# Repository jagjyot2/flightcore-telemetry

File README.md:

# FlightCore — Modular ESP32 Drone Sensor & 433 MHz LoRa Telemetry System

> **STRICT SAFETY CONSTRAINT**: FlightCore is **exclusively a passive sensor acquisition and LoRa telemetry expansion module**. It contains **NO motor/ESC PWM control, NO servo actuation, and NO flight controller stabilization loops**.

---

## System Overview

FlightCore attaches cleanly inline with a `2S–6S` (`7.4 V – 25.2 V`) UAV power bus to acquire inertial attitude, frame vibration, laser altitude, rotor RPM, pack voltage/current/mAh consumption, and thermal probe telemetry, streaming compact **37-byte CRC-16-CCITT binary frames** over **433 MHz LoRa** (`SX1278 Ra-02`) to a companion Python ground station.

```mermaid
flowchart LR
    subgraph Airframe["Airframe Sensors & Power Tap (Strictly Telemetry)"]
        VBAT["2S-6S LiPo -> 1mOhm Shunt + INA180A2 + 100k/10k Div"]
        IMU["MPU6050 IMU (I2C 0x68)"]
        TOF["VL53L0X ToF Laser (I2C 0x29)"]
        HALL["A3144 Hall RPM (ISR GPIO33)"]
        NTC["10k B3950 NTC Probe (GPIO36)"]
    end

    ESP["ESP32 DevKit v1 Firmware (200Hz IMU / 25Hz ToF / 5Hz RF)"]
    LORA["SX1278 433MHz LoRa (VSPI + 50-Ohm SMA)"]
    CAM["ESP32-CAM UART2 Stub (GPIO16/17)"]
    GS["Python Ground Station CLI (CRC-16-CCITT Decoder)"]

    VBAT --> ESP
    IMU --> ESP
    TOF --> ESP
    HALL --> ESP
    NTC --> ESP
    ESP <--> CAM
    ESP --> LORA
    LORA -->|"37B Binary Frame (0xFC 0x01)"| GS
```

---

## Key Engineering Highlights

- **Modular C++17 Firmware (`firmware/`)**:
  - **MPU6050 Driver** ([mpu6050_driver.cpp](firmware/src/mpu6050_driver.cpp)): `400 kHz` I2C, `250`-sample startup bias calibration, complementary roll/pitch filter (`α = 0.98`), and `32`-sample DC-mean-subtracted frame vibration RMS (`mg`).
  - **VL53L0X ToF Driver** ([vl53l0x_driver.cpp](firmware/src/vl53l0x_driver.cpp)): Non-blocking register-level driver with `XSHUT` hardware reset, `5`-tap median + EMA glitch rejection, and timeout diagnostics.
  - **SX1278 433 MHz LoRa Driver & Protocol** ([lora_sx1278.cpp](firmware/src/lora_sx1278.cpp), [telemetry_protocol.cpp](firmware/src/telemetry_protocol.cpp)): `0xFC 0x01` framed 37-byte binary protocol with sequence counter, `CRC-16-CCITT (0x1021/0xFFFF)`, configurable interval (`100–10000 ms`), non-blocking TX retry state machine, and RSSI/SNR link tracking.
  - **Hall-Effect RPM Driver** ([hall_rpm_driver.cpp](firmware/src/hall_rpm_driver.cpp)): `IRAM_ATTR` critical-section ISR on `GPIO33` with `350 µs` glitch debounce, configurable PPR, and timeout zeroing.
  - **Power & Thermal Monitor** ([power_temp_monitor.cpp](firmware/src/power_temp_monitor.cpp)): `16×` oversampled calibrated `ADC1` reads (`VBAT`, `INA180A2` `50 mV/A` current + trapezoidal `mAh` integrator, 3-term Steinhart-Hart NTC temperature).
  - **Diagnostics CLI & ESP32-CAM Bridge** ([main.cpp](firmware/src/main.cpp)): Non-blocking USB Serial CLI (`status`, `json`, `bin`, `hex`, `interval <ms>`, `cal imu`, `reset mah`, `ppr <n>`, `cam ping`) + `UART2` heartbeat bridge stub.
- **Ground Station Decoder (`ground_station/`)**:
  - Byte-exact Python implementation ([protocol.py](ground_station/protocol.py), [receiver_cli.py](ground_station/receiver_cli.py)) supporting live serial (`--serial`), hex dump (`--hex`), binary log playback (`--file`), and synthetic noisy stream simulation (`--simulate --inject-noise`).
- **Manufacturing-Ready KiCad 8 Hardware (`hardware/`)**:
  - Complete schematic, 2-layer `96.0 × 68.0 mm` PCB, netlist, RS-274X Gerbers + Excellon drill (`hardware/gerbers/`), geometric DRC report (`0 errors`), verified BOM ([BOM.csv](hardware/BOM.csv)), [PIN-MAPPING.md](hardware/PIN-MAPPING.md), [POWER-ARCHITECTURE.md](hardware/POWER-ARCHITECTURE.md), and [ASSEMBLY-GUIDE.md](hardware/ASSEMBLY-GUIDE.md).
- **Simulator-Independent Abstraction & Wokwi Simulation (`simulation/`, `wokwi/`)**:
  - Canonical simulator-agnostic sensor/transport interface ([sensor_bus_adapter.h](simulation/adapters/common/sensor_bus_adapter.h), [sensor_bus_adapter.py](simulation/adapters/common/sensor_bus_adapter.py)), deterministic flight/fault scenarios (`simulation/scenarios/`), and explicit [COMPONENT-SUPPORT-MATRIX.md](simulation/documentation/COMPONENT-SUPPORT-MATRIX.md).
  - **Active Wokwi Configuration (`wokwi/`)**: `board-esp32-devkit-c-v4` wired to `wokwi-mpu6050`, `wokwi-ntc-temperature-sensor`, `wokwi-potentiometer` (`VBAT`/`IBAT`), `wokwi-pushbutton` (`HALL_PULSE`/`CAL`), `wokwi-led`, and custom Wokwi chip stubs `chip-vl53l0x` and `chip-sx1278` executing `firmware/.pio/build/esp32dev/firmware.elf`.
- **BenchTwin & 3D CAD Staging (`benchtwin/` — Preserved)**:
  - Structured circuit graph (`flightcore-benchtwin.json`, `flightcore.btw`), vector schematic (`schematic_preview.svg`), simulation notes ([BENCHTWIN-SIMULATION-NOTES.md](benchtwin/BENCHTWIN-SIMULATION-NOTES.md)), and watertight closed-manifold 3D-printable mount (`enclosure_mount.stl`), indexed via [benchtwin_adapter_manifest.json](simulation/adapters/benchtwin/benchtwin_adapter_manifest.json) for future reactivation.

---

## Repository Structure

```
04-FLIGHTCORE/
├── firmware/           # PlatformIO ESP32 C++17 modular drivers, main loop & native C++ tests
├── ground_station/     # Python binary CRC-16-CCITT telemetry decoder & CLI
├── hardware/           # KiCad 8 project, Gerbers, DRC report, BOM & hardware guides
├── simulation/         # Simulator-agnostic adapters (common, wokwi, benchtwin), scenarios & matrix
├── wokwi/              # Active Wokwi diagram.json, wokwi.toml & custom chip stubs (VL53L0X/SX1278)
├── benchtwin/          # Preserved BenchTwin circuit graph/bundle, STL mount & SVG preview
├── tests/              # Automated pytest verification (protocol, math, C++ native, Wokwi, KiCad/STL)
├── docs/               # Detailed system architecture & protocol specs
├── ROADMAP.md          # Engineering phases & passive telemetry roadmap
└── LICENSE             # MIT License
```

---

## Quickstart & Verification

### 1. Build ESP32 Firmware & Static Check (PlatformIO)
```powershell
cd firmware
pio run -e esp32dev
pio check --skip-packages
```

### 2. Run Full Automated Verification Suite (Pytest + Compiled C++17 Native Tests)
```powershell
pytest -v
```
Verifies CRC-16-CCITT, binary encode/decode roundtrips, stream resynchronization, Steinhart-Hart NTC math, complementary filter convergence, vibration RMS, ToF median+EMA glitch rejection, Hall RPM debouncing, strict telemetry-only safety boundary, compiled C++ native tests (`firmware/test/test_flightcore_native.cpp`), KiCad S-expression validity, RS-274X Gerbers, DRC report, BOM/netlist parity, and STL closed-manifold geometry.

### 3. Run Ground Station Decoder CLI Without Hardware
```powershell
python -m ground_station.receiver_cli --simulate --count 6 --inject-noise --format table
```

### 4. Run Active Wokwi Simulation
1. Build firmware (`pio run -e esp32dev` in `firmware/`).
2. Open `wokwi/` in VS Code with the Wokwi extension (or run `wokwi-cli wokwi` with `$env:WOKWI_CLI_TOKEN` set). See [wokwi/README.md](wokwi/README.md) and [simulation/documentation/COMPONENT-SUPPORT-MATRIX.md](simulation/documentation/COMPONENT-SUPPORT-MATRIX.md).

#### Wokwi Component Support Summary
| Component | Wokwi Status | Simulation Representation |
|---|---|---|
| `ESP32 DevKit v1` (`U1`) | Native | `board-esp32-devkit-c-v4` |
| `MPU6050` (`U2`) | Native | `wokwi-mpu6050` (`I2C 0x68`) |
| `10k NTC` (`RT1`) & `SW1` / `D4` | Native | `wokwi-ntc-temperature-sensor`, `wokwi-pushbutton`, `wokwi-led` |
| `VBAT` Divider / `INA180A2` | Analog Stand-In | `wokwi-potentiometer` (`GPIO34` / `GPIO35`) |
| `VL53L0X` (`U3`) & `SX1278` (`U4`) | Unsupported Natively -> Custom Chip Stubs | `wokwi/chips/chip-vl53l0x.*` & `chip-sx1278.*` |
| `A3144` Hall (`U8`) & `ESP32-CAM` (`J6`) | Unsupported Natively -> Pulse/SW Stubs | `wokwi-pushbutton` (`GPIO33`) & UART2 software stub |

#### Future BenchTwin Reactivation
`benchtwin/` is preserved untouched. To reactivate BenchTwin for electrical/3D inspection, open `benchtwin/flightcore.btw` (see [simulation/adapters/benchtwin/README.md](simulation/adapters/benchtwin/README.md)).

---

## Hardware BOM Summary

| Subsystem | Key Part | Interface / Rating | Designator |
|---|---|---|---|
| MCU | DOIT ESP32 DevKit v1 (30-pin) | `3.3 V` IO / `5 V` VIN | `U1` |
| 6-Axis IMU | MPU6050 (GY-521) | `I2C 0x68` @ `400 kHz` | `U2` |
| ToF Ranging | VL53L0X (GY-VL53L0XV2) | `I2C 0x29`, `XSHUT=GPIO26` | `U3` |
| 433 MHz LoRa | AI-Thinker Ra-02 (SX1278) | `VSPI`, `+17 dBm`, Edge SMA `J5` | `U4` |
| Current Sense | `1 mΩ 3W 2512` Shunt + `INA180A2` | `50 mV/A`, `V_CM <= 26 V` | `R11`, `U5` |
| Power Rails | `MP1584 5V/3A Buck` + `AMS1117-3.3` | `2S–6S LiPo` + PTC/Schottky/TVS | `U7`, `U6`, `F1`, `D1`, `D3` |
| RPM & Thermal | `A3144EUA-T` Hall + `10 kΩ B3950 NTC` | `GPIO33` ISR / `GPIO36` ADC1 | `U8`, `RT1` |

See [hardware/BOM.csv](hardware/BOM.csv) and [hardware/ASSEMBLY-GUIDE.md](hardware/ASSEMBLY-GUIDE.md) for complete assembly instructions and the mandatory **`JP1` power jumper rule**.

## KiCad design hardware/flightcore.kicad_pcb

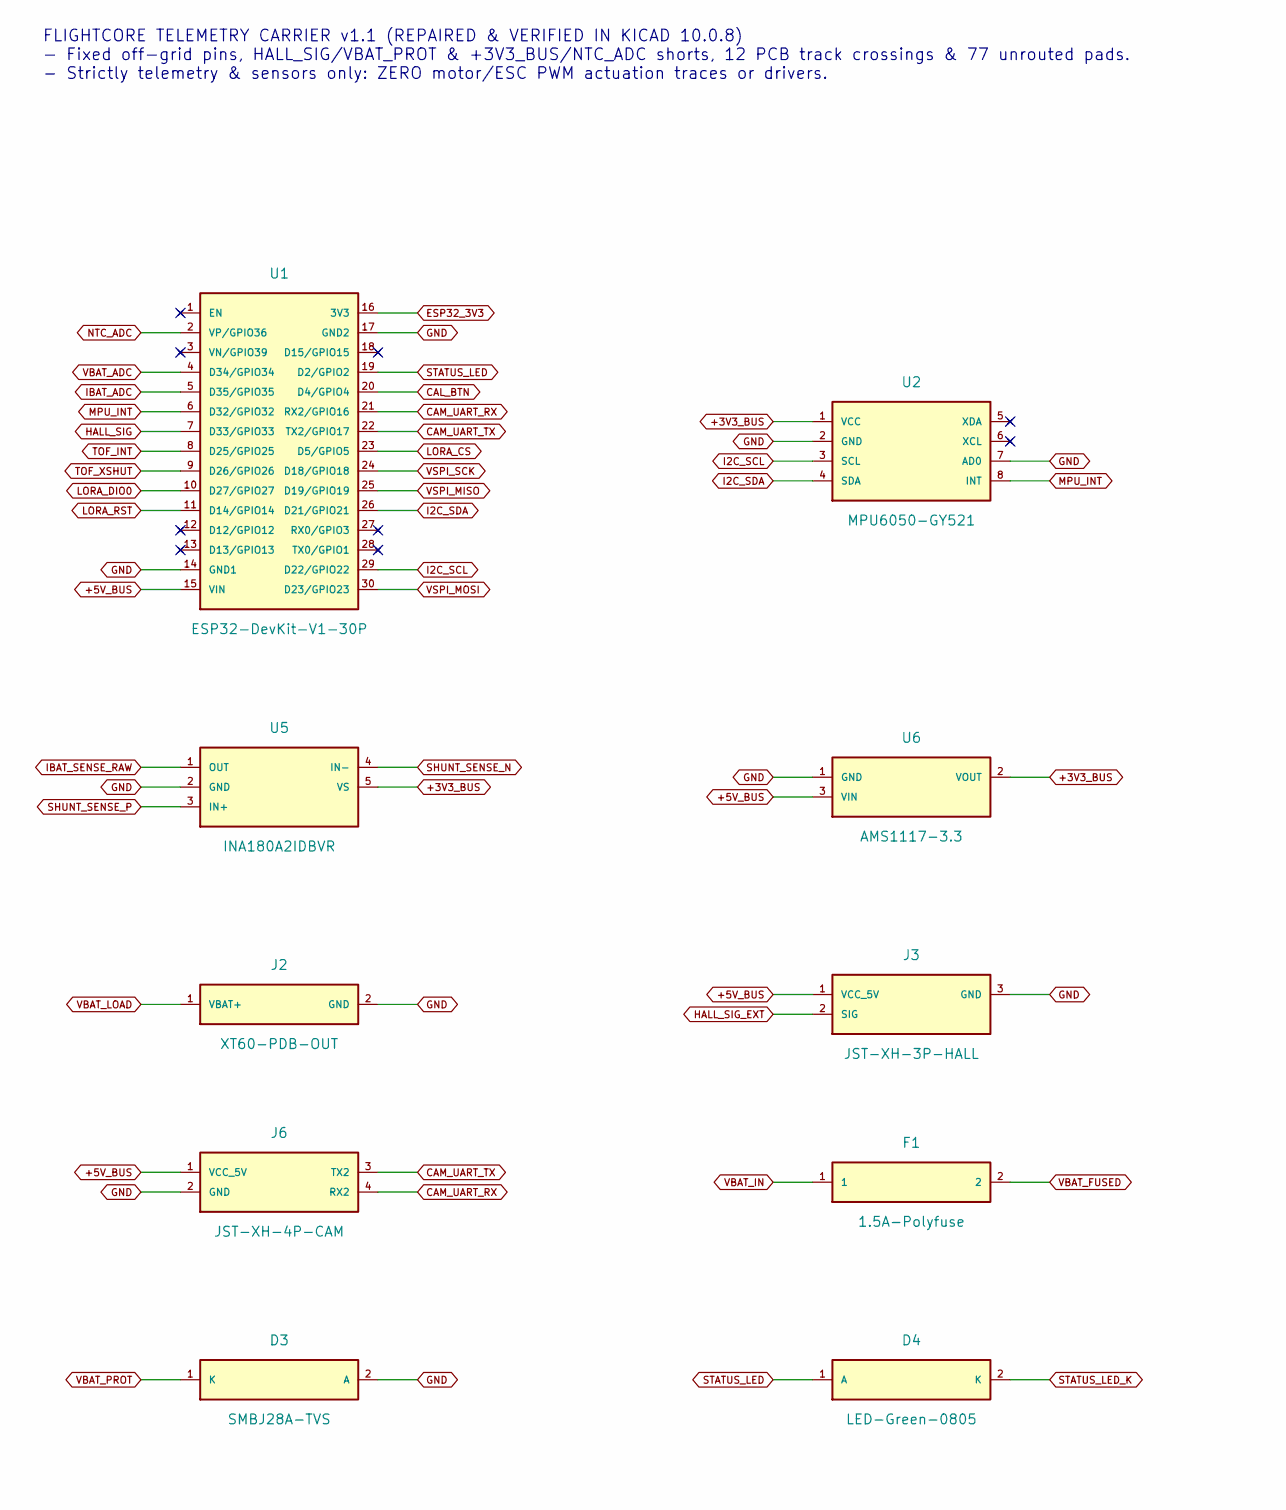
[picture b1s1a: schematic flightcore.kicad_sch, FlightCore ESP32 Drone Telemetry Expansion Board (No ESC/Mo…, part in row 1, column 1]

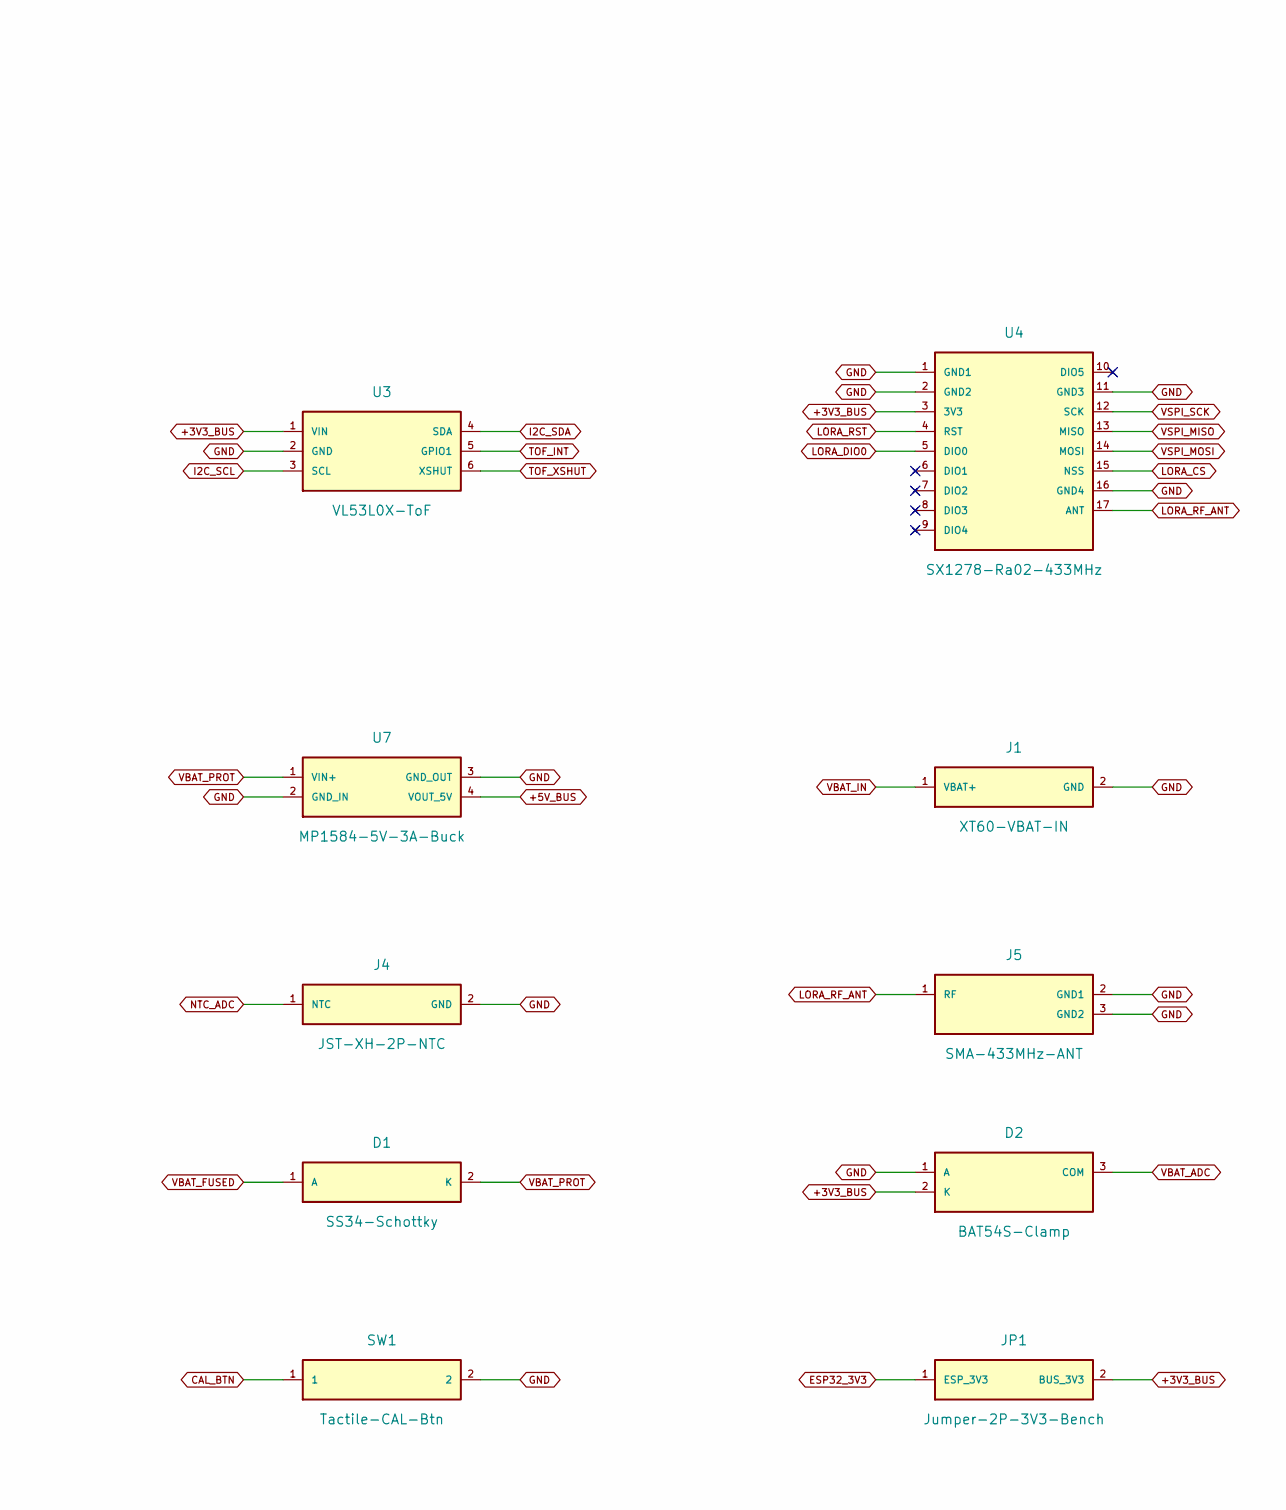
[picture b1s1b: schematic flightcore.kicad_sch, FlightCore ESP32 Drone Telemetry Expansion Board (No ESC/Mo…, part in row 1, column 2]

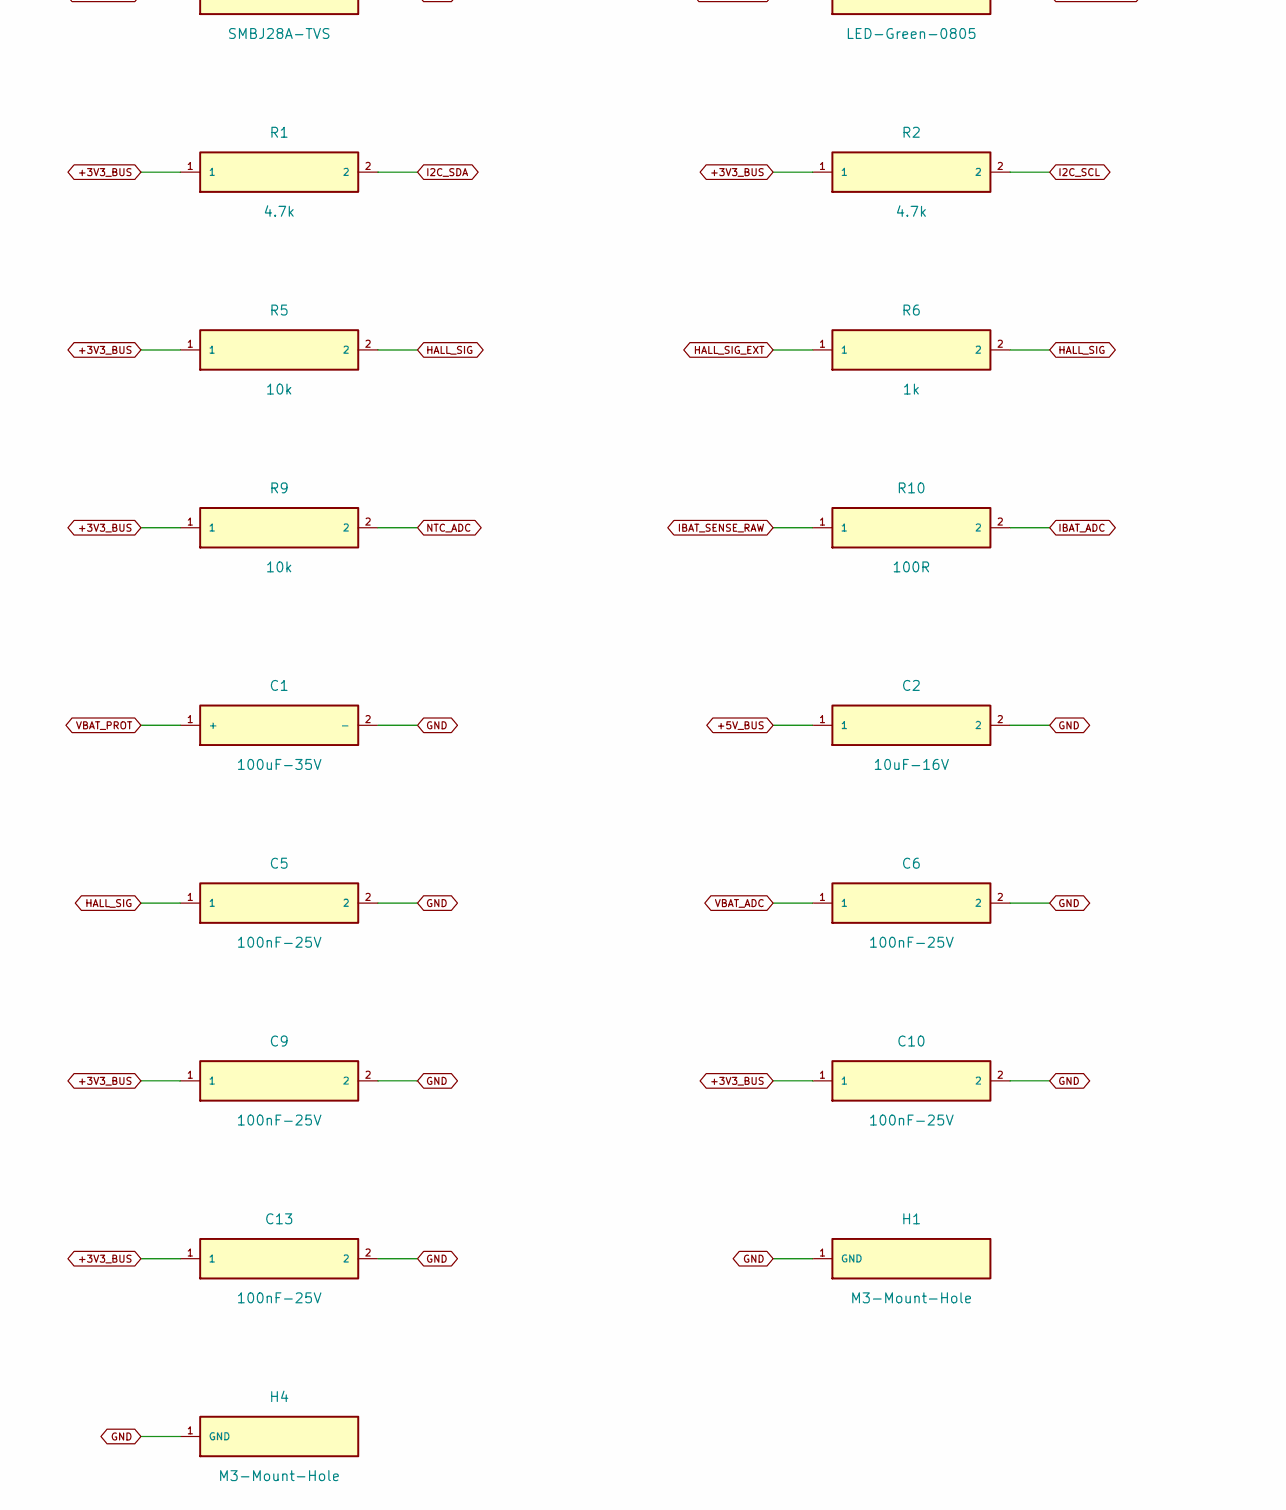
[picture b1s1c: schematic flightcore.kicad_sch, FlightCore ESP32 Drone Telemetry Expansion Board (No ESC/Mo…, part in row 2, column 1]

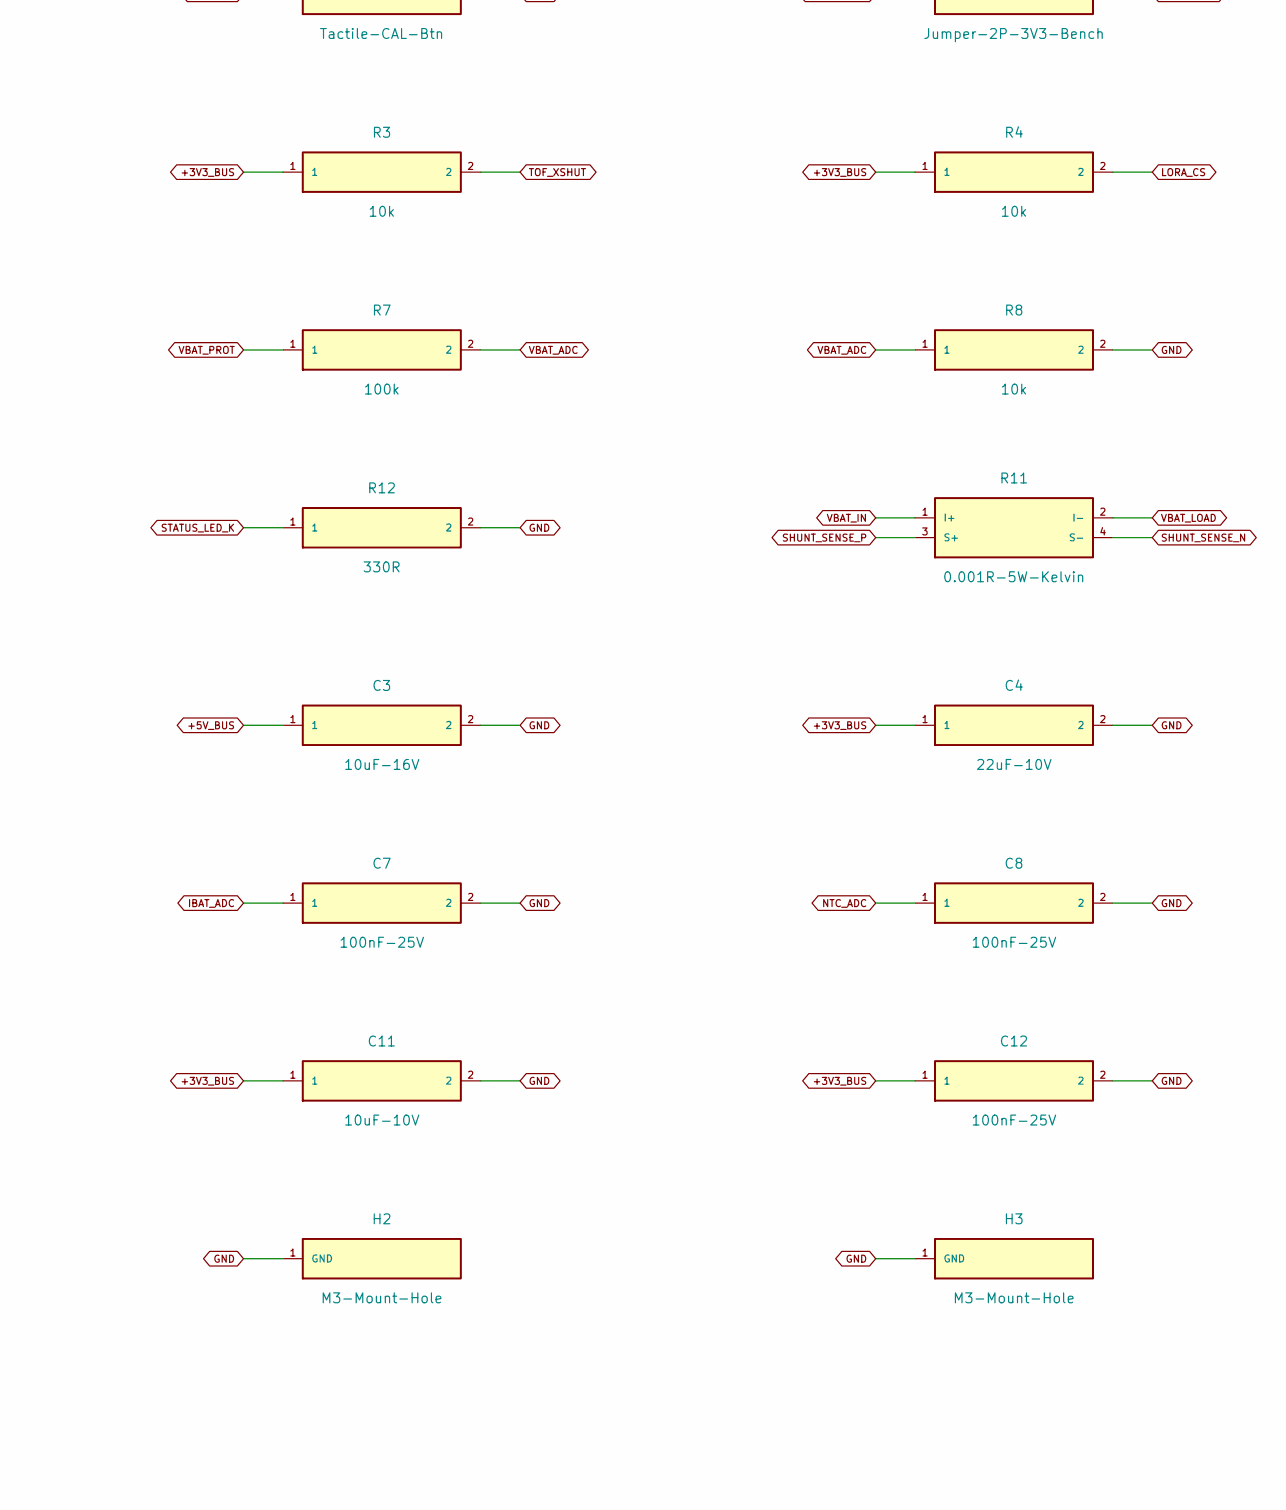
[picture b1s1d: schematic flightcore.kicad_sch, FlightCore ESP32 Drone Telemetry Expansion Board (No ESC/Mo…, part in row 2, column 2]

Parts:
C1: 100uF-35V; CP_Radial_D6.3mm; Rating 35V / 100uF
C2, C3: 10uF-16V; SMD_0805; Rating 16V
C4: 22uF-10V; SMD_0805; Rating 10V
C5, C6, C7, C8, C9, C10, C12, C13: 100nF-25V; SMD_0805; Rating 25V
C11: 10uF-10V; SMD_0805; Rating 10V
D1: SS34-Schottky; D_SMA; Rating 40V / 3A; MPN SS34
D2: BAT54S-Clamp; SOT-23; Rating 30V / 200mA; MPN BAT54S
D3: SMBJ28A-TVS; D_SMB; Rating 28V / 600W; MPN SMBJ28A
D4: LED-Green-0805; SMD_0805; Rating 2.1V / 20mA; MPN APT2012CGCK
F1: 1.5A-Polyfuse; SMD_1206; Rating 30V / 1.5A; MPN 1206L150
H1, H2, H3, H4: M3-Mount-Hole; MountingHole_3.2mm_M3_Pad_Via; Rating M3
J1: XT60-VBAT-IN; AMASS_XT60_Vertical; Rating 60A / 25.2V; MPN XT60-M
J2: XT60-PDB-OUT; AMASS_XT60_Vertical; Rating 60A / 25.2V; MPN XT60-F
J3: JST-XH-3P-HALL; JST_XH_B3B-XH-A_1x03_P2.50mm_Vertical; Rating 5V / 1A; MPN B3B-XH-A
J4: JST-XH-2P-NTC; JST_XH_B2B-XH-A_1x02_P2.50mm_Vertical; Rating 3.3V / 1A; MPN B2B-XH-A
J5: SMA-433MHz-ANT; SMA_EdgeMount; Rating 50 Ohm / 433MHz; MPN 132289
J6: JST-XH-4P-CAM; JST_XH_B4B-XH-A_1x04_P2.50mm_Vertical; Rating 5V / 500mA; MPN B4B-XH-A
JP1: Jumper-2P-3V3-Bench; PinHeader_1x02_P2.54mm; Rating 3.3V / 1A; MPN PinHeader_1x02
R1, R2: 4.7k; SMD_0805; Rating 50V / 0.125W
R3, R4, R5, R8, R9: 10k; SMD_0805; Rating 50V / 0.125W
R6: 1k; SMD_0805; Rating 50V / 0.125W
R7: 100k; SMD_0805; Rating 50V / 0.125W
R10: 100R; SMD_0805; Rating 50V / 0.125W
R11: 0.001R-5W-Kelvin; R_Shunt_4Wire_CSS4J_4026; Rating 1mOhm / 5W Kelvin; MPN CSS4J-4026R-1L00F
R12: 330R; SMD_0805; Rating 50V / 0.125W
SW1: Tactile-CAL-Btn; SW_SPST_SMD; Rating 12V / 50mA; MPN PTS645
U1: ESP32-DevKit-V1-30P; ESP32_DevKit_V1_30P; Rating 3.3V IO / 5V VIN; MPN ESP32-DevKit-V1-30P
U2: MPU6050-GY521; PinHeader_1x08_P2.54mm; Rating 3.3V / I2C 400kHz; MPN GY-521
U3: VL53L0X-ToF; PinHeader_1x06_P2.54mm; Rating 3.3V / I2C 0x29; MPN GY-VL53L0XV2
U4: SX1278-Ra02-433MHz; Ai_Thinker_Ra02; Rating 3.3V / +20dBm; MPN Ra-02-SX1278
U5: INA180A2IDBVR; SOT-23-5; Rating 50V/V, Vcm 26V; MPN INA180A2IDBVR
U6: AMS1117-3.3; SOT-223-3_TabPin2; Rating 3.3V / 1.0A; MPN AMS1117-3.3
U7: MP1584-5V-3A-Buck; Buck_5V_3A_Module; Rating 7-28V -> 5V/3A; MPN MP1584EN-5V

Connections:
+3V3_BUS: C4.1, C9.1, C10.1, C11.1, C12.1, C13.1, D2.2 (K), JP1.2 (BUS_3V3), R1.1, R2.1, R3.1, R4.1, R5.1, R9.1, U2.1 (VCC), U3.1 (VIN), U4.3 (3V3), U5.5 (VS), U6.2 (VOUT)
+5V_BUS: C2.1, C3.1, J3.1 (VCC_5V), J6.1 (VCC_5V), U1.15 (VIN), U6.3 (VIN), U7.4 (VOUT_5V)
CAL_BTN: SW1.1, U1.20 (D4/GPIO4)
CAM_UART_RX: J6.4 (RX2), U1.21 (RX2/GPIO16)
CAM_UART_TX: J6.3 (TX2), U1.22 (TX2/GPIO17)
ESP32_3V3: JP1.1 (ESP_3V3), U1.16 (3V3)
GND: C1.2 (-), C2.2, C3.2, C4.2, C5.2, C6.2, C7.2, C8.2, C9.2, C10.2, C11.2, C12.2, C13.2, D2.1 (A), D3.2 (A), H1.1, H2.1, H3.1, H4.1, J1.2 (GND), J2.2 (GND), J3.3 (GND), J4.2 (GND), J5.2 (GND1), J5.3 (GND2), J6.2 (GND), R8.2, R12.2, SW1.2, U1.14 (GND1), U1.17 (GND2), U2.2 (GND), U2.7 (AD0), U3.2 (GND), U4.1 (GND1), U4.2 (GND2), U4.11 (GND3), U4.16 (GND4), U5.2 (GND), U6.1 (GND), U7.2 (GND_IN), U7.3 (GND_OUT)
HALL_SIG: C5.1, R5.2, R6.2, U1.7 (D33/GPIO33)
HALL_SIG_EXT: J3.2 (SIG), R6.1
I2C_SCL: R2.2, U1.29 (D22/GPIO22), U2.3 (SCL), U3.3 (SCL)
I2C_SDA: R1.2, U1.26 (D21/GPIO21), U2.4 (SDA), U3.4 (SDA)
IBAT_ADC: C7.1, R10.2, U1.5 (D35/GPIO35)
IBAT_SENSE_RAW: R10.1, U5.1 (OUT)
LORA_CS: R4.2, U1.23 (D5/GPIO5), U4.15 (NSS)
LORA_DIO0: U1.10 (D27/GPIO27), U4.5 (DIO0)
LORA_RF_ANT: J5.1 (RF), U4.17 (ANT)
LORA_RST: U1.11 (D14/GPIO14), U4.4 (RST)
MPU_INT: U1.6 (D32/GPIO32), U2.8 (INT)
NTC_ADC: C8.1, J4.1 (NTC), R9.2, U1.2 (VP/GPIO36)
SHUNT_SENSE_N: R11.4 (S-), U5.4 (IN-)
SHUNT_SENSE_P: R11.3 (S+), U5.3 (IN+)
STATUS_LED: D4.1 (A), U1.19 (D2/GPIO2)
STATUS_LED_K: D4.2 (K), R12.1
TOF_INT: U1.8 (D25/GPIO25), U3.5 (GPIO1)
TOF_XSHUT: R3.2, U1.9 (D26/GPIO26), U3.6 (XSHUT)
VBAT_ADC: C6.1, D2.3 (COM), R7.2, R8.1, U1.4 (D34/GPIO34)
VBAT_FUSED: D1.1 (A), F1.2
VBAT_IN: F1.1, J1.1 (VBAT+), R11.1 (I+)
VBAT_LOAD: J2.1 (VBAT+), R11.2 (I-)
VBAT_PROT: C1.1 (+), D1.2 (K), D3.1 (K), R7.1, U7.1 (VIN+)
VSPI_MISO: U1.25 (D19/GPIO19), U4.13 (MISO)
VSPI_MOSI: U1.30 (D23/GPIO23), U4.14 (MOSI)
VSPI_SCK: U1.24 (D18/GPIO18), U4.12 (SCK)

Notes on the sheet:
FLIGHTCORE TELEMETRY CARRIER v1.1 (REPAIRED & VERIFIED IN KICAD 10.0.8) - Fixed off-grid pins, HALL_SIG/VBAT_PROT & +3V3_BUS/NTC_ADC shorts, 12 PCB track crossings & 77 unrouted pads. - Strictly telemetry & sensors only: ZERO motor/ESC PWM actuation traces or drivers.

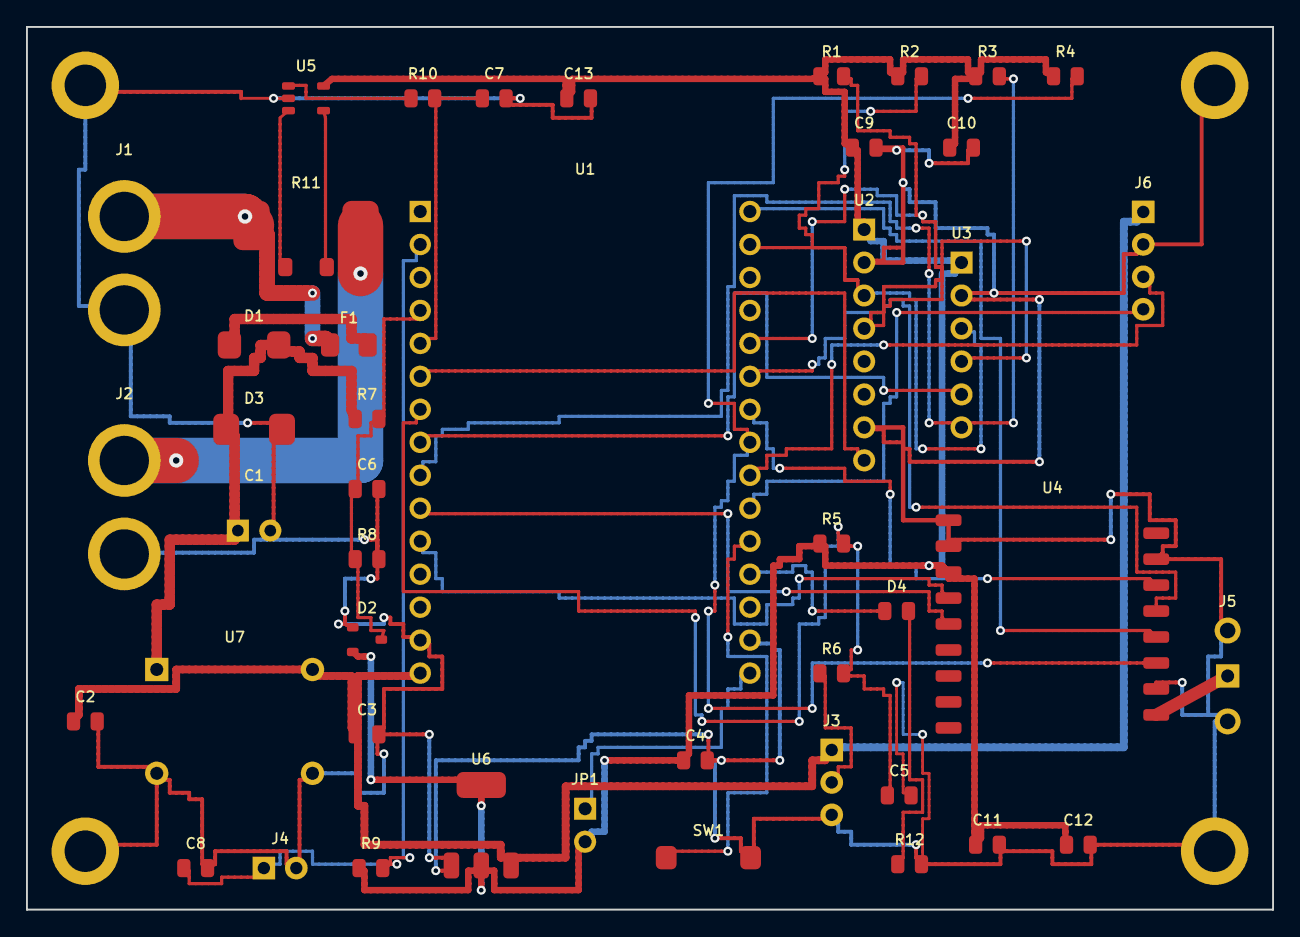
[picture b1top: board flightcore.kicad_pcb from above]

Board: 2 copper layers, 96.0 x 68.0 mm, 49 parts (0 on the bottom side), 33 nets.

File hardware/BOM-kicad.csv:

"Designator","Value","Footprint","MPN","Manufacturer","Rating","Qty"
"C1","100uF-35V","FlightCore:CP_Radial_D6.3mm","","","35V / 100uF","1"
"C2","10uF-16V","FlightCore:SMD_0805","","","16V","1"
"C3","10uF-16V","FlightCore:SMD_0805","","","16V","1"
"C4","22uF-10V","FlightCore:SMD_0805","","","10V","1"
"C5","100nF-25V","FlightCore:SMD_0805","","","25V","1"
"C6","100nF-25V","FlightCore:SMD_0805","","","25V","1"
"C7","100nF-25V","FlightCore:SMD_0805","","","25V","1"
"C8","100nF-25V","FlightCore:SMD_0805","","","25V","1"
"C9","100nF-25V","FlightCore:SMD_0805","","","25V","1"
"C10","100nF-25V","FlightCore:SMD_0805","","","25V","1"
"C11","10uF-10V","FlightCore:SMD_0805","","","10V","1"
"C12","100nF-25V","FlightCore:SMD_0805","","","25V","1"
"C13","100nF-25V","FlightCore:SMD_0805","","","25V","1"
"D1","SS34-Schottky","FlightCore:D_SMA","SS34","Vishay","40V / 3A","1"
"D2","BAT54S-Clamp","FlightCore:SOT-23","BAT54S","Diodes Inc","30V / 200mA","1"
"D3","SMBJ28A-TVS","FlightCore:D_SMB","SMBJ28A","Littelfuse","28V / 600W","1"
"D4","LED-Green-0805","FlightCore:SMD_0805","APT2012CGCK","Kingbright","2.1V / 20mA","1"
"F1","1.5A-Polyfuse","FlightCore:SMD_1206","1206L150","Littelfuse","30V / 1.5A","1"
"H1","M3-Mount-Hole","FlightCore:MountingHole_3.2mm_M3_Pad_Via","","","M3","1"
"H2","M3-Mount-Hole","FlightCore:MountingHole_3.2mm_M3_Pad_Via","","","M3","1"
"H3","M3-Mount-Hole","FlightCore:MountingHole_3.2mm_M3_Pad_Via","","","M3","1"
"H4","M3-Mount-Hole","FlightCore:MountingHole_3.2mm_M3_Pad_Via","","","M3","1"
"J1","XT60-VBAT-IN","FlightCore:AMASS_XT60_Vertical","XT60-M","Amass","60A / 25.2V","1"
"J2","XT60-PDB-OUT","FlightCore:AMASS_XT60_Vertical","XT60-F","Amass","60A / 25.2V","1"
"J3","JST-XH-3P-HALL","FlightCore:JST_XH_B3B-XH-A_1x03_P2.50mm_Vertical","B3B-XH-A","JST","5V / 1A","1"
"J4","JST-XH-2P-NTC","FlightCore:JST_XH_B2B-XH-A_1x02_P2.50mm_Vertical","B2B-XH-A","JST","3.3V / 1A","1"
"J5","SMA-433MHz-ANT","FlightCore:SMA_EdgeMount","132289","Amphenol","50 Ohm / 433MHz","1"
"J6","JST-XH-4P-CAM","FlightCore:JST_XH_B4B-XH-A_1x04_P2.50mm_Vertical","B4B-XH-A","JST","5V / 500mA","1"
"JP1","Jumper-2P-3V3-Bench","FlightCore:PinHeader_1x02_P2.54mm","PinHeader_1x02","Generic","3.3V / 1A","1"
"R1","4.7k","FlightCore:SMD_0805","","","50V / 0.125W","1"
"R2","4.7k","FlightCore:SMD_0805","","","50V / 0.125W","1"
"R3","10k","FlightCore:SMD_0805","","","50V / 0.125W","1"
"R4","10k","FlightCore:SMD_0805","","","50V / 0.125W","1"
"R5","10k","FlightCore:SMD_0805","","","50V / 0.125W","1"
"R6","1k","FlightCore:SMD_0805","","","50V / 0.125W","1"
"R7","100k","FlightCore:SMD_0805","","","50V / 0.125W","1"
"R8","10k","FlightCore:SMD_0805","","","50V / 0.125W","1"
"R9","10k","FlightCore:SMD_0805","","","50V / 0.125W","1"
"R10","100R","FlightCore:SMD_0805","","","50V / 0.125W","1"
"R11","0.001R-5W-Kelvin","FlightCore:R_Shunt_4Wire_CSS4J_4026","CSS4J-4026R-1L00F","Bourns","1mOhm / 5W Kelvin","1"
"R12","330R","FlightCore:SMD_0805","","","50V / 0.125W","1"
"SW1","Tactile-CAL-Btn","FlightCore:SW_SPST_SMD","PTS645","C&K","12V / 50mA","1"
"U1","ESP32-DevKit-V1-30P","FlightCore:ESP32_DevKit_V1_30P","ESP32-DevKit-V1-30P","Espressif","3.3V IO / 5V VIN","1"
"U2","MPU6050-GY521","FlightCore:PinHeader_1x08_P2.54mm","GY-521","InvenSense","3.3V / I2C 400kHz","1"
"U3","VL53L0X-ToF","FlightCore:PinHeader_1x06_P2.54mm","GY-VL53L0XV2","STMicroelectronics","3.3V / I2C 0x29","1"
"U4","SX1278-Ra02-433MHz","FlightCore:Ai_Thinker_Ra02","Ra-02-SX1278","Ai-Thinker","3.3V / +20dBm","1"
"U5","INA180A2IDBVR","FlightCore:SOT-23-5","INA180A2IDBVR","Texas Instruments","50V/V, Vcm 26V","1"
"U6","AMS1117-3.3","FlightCore:SOT-223-3_TabPin2","AMS1117-3.3","AMS","3.3V / 1.0A","1"
"U7","MP1584-5V-3A-Buck","FlightCore:Buck_5V_3A_Module","MP1584EN-5V","MPS","7-28V -> 5V/3A","1"

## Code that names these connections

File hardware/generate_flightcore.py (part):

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        25.4,
        15.24,
        "FLIGHTCORE TELEMETRY CARRIER v1.1 (REPAIRED & VERIFIED IN KICAD 10.0.8)\n"
        "- Fixed off-grid pins, HALL_SIG/VBAT_PROT & +3V3_BUS/NTC_ADC shorts, 12 PCB track crossings & 77 unrouted pads.\n"
        "- Strictly telemetry & sensors only: ZERO motor/ESC PWM actuation traces or drivers.",
    )

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            f"{LIB}:ESP32_DevKit_V1_30P",
            [
                kt.SchPin("1", "EN", "NC_EN", "left", "no_connect"),
                kt.SchPin("2", "VP/GPIO36", "NTC_ADC", "left"),
                kt.SchPin("3", "VN/GPIO39", "NC_VN", "left", "no_connect"),
                kt.SchPin("4", "D34/GPIO34", "VBAT_ADC", "left"),
                kt.SchPin("5", "D35/GPIO35", "IBAT_ADC", "left"),
                kt.SchPin("6", "D32/GPIO32", "MPU_INT", "left"),
                kt.SchPin("7", "D33/GPIO33", "HALL_SIG", "left"),
                kt.SchPin("8", "D25/GPIO25", "TOF_INT", "left"),
                kt.SchPin("9", "D26/GPIO26", "TOF_XSHUT", "left"),
                kt.SchPin("10", "D27/GPIO27", "LORA_DIO0", "left"),
                kt.SchPin("11", "D14/GPIO14", "LORA_RST", "left"),
                kt.SchPin("12", "D12/GPIO12", "NC_D12", "left", "no_connect"),
                kt.SchPin("13", "D13/GPIO13", "NC_D13", "left", "no_connect"),
                kt.SchPin("14", "GND1", "GND", "left"),
                kt.SchPin("15", "VIN", "+5V_BUS", "left"),
                kt.SchPin("16", "3V3", "ESP32_3V3", "right"),
                kt.SchPin("17", "GND2", "GND", "right"),
                kt.SchPin("18", "D15/GPIO15", "NC_D15", "right", "no_connect"),
                kt.SchPin("19", "D2/GPIO2", "STATUS_LED", "right"),
                kt.SchPin("20", "D4/GPIO4", "CAL_BTN", "right"),
                kt.SchPin("21", "RX2/GPIO16", "CAM_UART_RX", "right"),
                kt.SchPin("22", "TX2/GPIO17", "CAM_UART_TX", "right"),
                kt.SchPin("23", "D5/GPIO5", "LORA_CS", "right"),
                kt.SchPin("24", "D18/GPIO18", "VSPI_SCK", "right"),
                kt.SchPin("25", "D19/GPIO19", "VSPI_MISO", "right"),
                kt.SchPin("26", "D21/GPIO21", "I2C_SDA", "right"),
                kt.SchPin("27", "RX0/GPIO3", "NC_RX0", "right", "no_connect"),
                kt.SchPin("28", "TX0/GPIO1", "NC_TX0", "right", "no_connect"),
                kt.SchPin("29", "D22/GPIO22", "I2C_SCL", "right"),
                kt.SchPin("30", "D23/GPIO23", "VSPI_MOSI", "right"),
            ],
            mpn="ESP32-DevKit-V1-30P",
            manufacturer="Espressif",
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            [
                kt.SchPin("1", "VCC", "+3V3_BUS", "left"),
                kt.SchPin("2", "GND", "GND", "left"),
                kt.SchPin("3", "SCL", "I2C_SCL", "left"),
                kt.SchPin("4", "SDA", "I2C_SDA", "left"),
                kt.SchPin("5", "XDA", "NC_XDA", "right", "no_connect"),
                kt.SchPin("6", "XCL", "NC_XCL", "right", "no_connect"),
                kt.SchPin("7", "AD0", "GND", "right"),
                kt.SchPin("8", "INT", "MPU_INT", "right"),
            ],
            mpn="GY-521",
            manufacturer="InvenSense",
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            [
                kt.SchPin("1", "VIN", "+3V3_BUS", "left"),
                kt.SchPin("2", "GND", "GND", "left"),
                kt.SchPin("3", "SCL", "I2C_SCL", "left"),
                kt.SchPin("4", "SDA", "I2C_SDA", "right"),
                kt.SchPin("5", "GPIO1", "TOF_INT", "right"),
                kt.SchPin("6", "XSHUT", "TOF_XSHUT", "right"),
            ],
            mpn="GY-VL53L0XV2",
            manufacturer="STMicroelectronics",
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                kt.SchPin("1", "GND1", "GND", "left"),
                kt.SchPin("2", "GND2", "GND", "left"),
                kt.SchPin("3", "3V3", "+3V3_BUS", "left"),
                kt.SchPin("4", "RST", "LORA_RST", "left"),
                kt.SchPin("5", "DIO0", "LORA_DIO0", "left"),
                kt.SchPin("6", "DIO1", "NC_DIO1", "left", "no_connect"),
                kt.SchPin("7", "DIO2", "NC_DIO2", "left", "no_connect"),
                kt.SchPin("8", "DIO3", "NC_DIO3", "left", "no_connect"),
                kt.SchPin("9", "DIO4", "NC_DIO4", "left", "no_connect"),
                kt.SchPin("10", "DIO5", "NC_DIO5", "right", "no_connect"),
                kt.SchPin("11", "GND3", "GND", "right"),
                kt.SchPin("12", "SCK", "VSPI_SCK", "right"),
                kt.SchPin("13", "MISO", "VSPI_MISO", "right"),
                kt.SchPin("14", "MOSI", "VSPI_MOSI", "right"),
                kt.SchPin("15", "NSS", "LORA_CS", "right"),
                kt.SchPin("16", "GND4", "GND", "right"),
                kt.SchPin("17", "ANT", "LORA_RF_ANT", "right"),
            ],
            mpn="Ra-02-SX1278",
            manufacturer="Ai-Thinker",
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            "INA180A2IDBVR",
            f"{LIB}:SOT-23-5",
            [
                kt.SchPin("1", "OUT", "IBAT_SENSE_RAW", "left"),
                kt.SchPin("2", "GND", "GND", "left"),
                kt.SchPin("3", "IN+", "SHUNT_SENSE_P", "left"),
                kt.SchPin("4", "IN-", "SHUNT_SENSE_N", "right"),
                kt.SchPin("5", "VS", "+3V3_BUS", "right"),
            ],
            mpn="INA180A2IDBVR",
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            "MP1584-5V-3A-Buck",
            f"{LIB}:Buck_5V_3A_Module",
            [
                kt.SchPin("1", "VIN+", "VBAT_PROT", "left"),
                kt.SchPin("2", "GND_IN", "GND", "left"),
                kt.SchPin("3", "GND_OUT", "GND", "right"),
                kt.SchPin("4", "VOUT_5V", "+5V_BUS", "right"),
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    )

    # Connectors & Protection
    sb.add_component(kt.SchComponent("J1", "XT60-VBAT-IN", f"{LIB}:AMASS_XT60_Vertical", [kt.SchPin("1", "VBAT+", "VBAT_IN", "left"), kt.SchPin("2", "GND", "GND", "right")], mpn="XT60-M", manufacturer="Amass", rating="60A / 25.2V"))
    sb.add_component(kt.SchComponent("J2", "XT60-PDB-OUT", f"{LIB}:AMASS_XT60_Vertical", [kt.SchPin("1", "VBAT+", "VBAT_LOAD", "left"), kt.SchPin("2", "GND", "GND", "right")], mpn="XT60-F", manufacturer="Amass", rating="60A / 25.2V"))
    sb.add_component(kt.SchComponent("J3", "JST-XH-3P-HALL", f"{LIB}:JST_XH_B3B-XH-A_1x03_P2.50mm_Vertical", [kt.SchPin("1", "VCC_5V", "+5V_BUS", "left"), kt.SchPin("2", "SIG", "HALL_SIG_EXT", "left"), kt.SchPin("3", "GND", "GND", "right")], mpn="B3B-XH-A", manufacturer="JST", rating="5V / 1A"))
    sb.add_component(kt.SchComponent("J4", "JST-XH-2P-NTC", f"{LIB}:JST_XH_B2B-XH-A_1x02_P2.50mm_Vertical", [kt.SchPin("1", "NTC", "NTC_ADC", "left"), kt.SchPin("2", "GND", "GND", "right")], mpn="B2B-XH-A", manufacturer="JST", rating="3.3V / 1A"))
    sb.add_component(kt.SchComponent("J5", "SMA-433MHz-ANT", f"{LIB}:SMA_EdgeMount", [kt.SchPin("1", "RF", "LORA_RF_ANT", "left"), kt.SchPin("2", "GND1", "GND", "right"), kt.SchPin("3", "GND2", "GND", "right")], mpn="132289", manufacturer="Amphenol", rating="50 Ohm / 433MHz"))
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
    sb.add_component(kt.SchComponent("F1", "1.5A-Polyfuse", f"{LIB}:SMD_1206", [kt.SchPin("1", "1", "VBAT_IN", "left"), kt.SchPin("2", "2", "VBAT_FUSED", "right")], mpn="1206L150", manufacturer="Littelfuse", rating="30V / 1.5A"))
    sb.add_component(kt.SchComponent("D1", "SS34-Schottky", f"{LIB}:D_SMA", [kt.SchPin("1", "A", "VBAT_FUSED", "left"), kt.SchPin("2", "K", "VBAT_PROT", "right")], mpn="SS34", manufacturer="Vishay", rating="40V / 3A"))
    sb.add_component(kt.SchComponent("D2", "BAT54S-Clamp", f"{LIB}:SOT-23", [kt.SchPin("1", "A", "GND", "left"), kt.SchPin("2", "K", "+3V3_BUS", "left"), kt.SchPin("3", "COM", "VBAT_ADC", "right")], mpn="BAT54S", manufacturer="Diodes Inc", rating="30V / 200mA"))
    sb.add_component(kt.SchComponent("D3", "SMBJ28A-TVS", f"{LIB}:D_SMB", [kt.SchPin("1", "K", "VBAT_PROT", "left"), kt.SchPin("2", "A", "GND", "right")], mpn="SMBJ28A", manufacturer="Littelfuse", rating="28V / 600W"))
    sb.add_component(kt.SchComponent("D4", "LED-Green-0805", f"{LIB}:SMD_0805", [kt.SchPin("1", "A", "STATUS_LED", "left"), kt.SchPin("2", "K", "STATUS_LED_K", "right")], mpn="APT2012CGCK", manufacturer="Kingbright", rating="2.1V / 20mA"))
    sb.add_component(kt.SchComponent("SW1", "Tactile-CAL-Btn", f"{LIB}:SW_SPST_SMD", [kt.SchPin("1", "1", "CAL_BTN", "left"), kt.SchPin("2", "2", "GND", "right")], mpn="PTS645", manufacturer="C&K", rating="12V / 50mA"))
    sb.add_component(kt.SchComponent("JP1", "Jumper-2P-3V3-Bench", f"{LIB}:PinHeader_1x02_P2.54mm", [kt.SchPin("1", "ESP_3V3", "ESP32_3V3", "left"), kt.SchPin("2", "BUS_3V3", "+3V3_BUS", "right")], mpn="PinHeader_1x02", manufacturer="Generic", rating="3.3V / 1A"))

    # Resistors
    resistors = [
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        sb.add_component(kt.SchComponent(ref, val, f"{LIB}:SMD_0805", [kt.SchPin("1", "1", n1, "left"), kt.SchPin("2", "2", n2, "right")], rating="50V / 0.125W"))

    sb.add_component(kt.SchComponent("R11", "0.001R-5W-Kelvin", f"{LIB}:R_Shunt_4Wire_CSS4J_4026", [
        kt.SchPin("1", "I+", "VBAT_IN", "left"),
        kt.SchPin("2", "I-", "VBAT_LOAD", "right"),
        kt.SchPin("3", "S+", "SHUNT_SENSE_P", "left"),
        kt.SchPin("4", "S-", "SHUNT_SENSE_N", "right"),
    ], mpn="CSS4J-4026R-1L00F", manufacturer="Bourns", rating="1mOhm / 5W Kelvin"))
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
